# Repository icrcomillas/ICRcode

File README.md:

#  ICRcode
Entorno de desarrollo del ICAI Club de Robótica

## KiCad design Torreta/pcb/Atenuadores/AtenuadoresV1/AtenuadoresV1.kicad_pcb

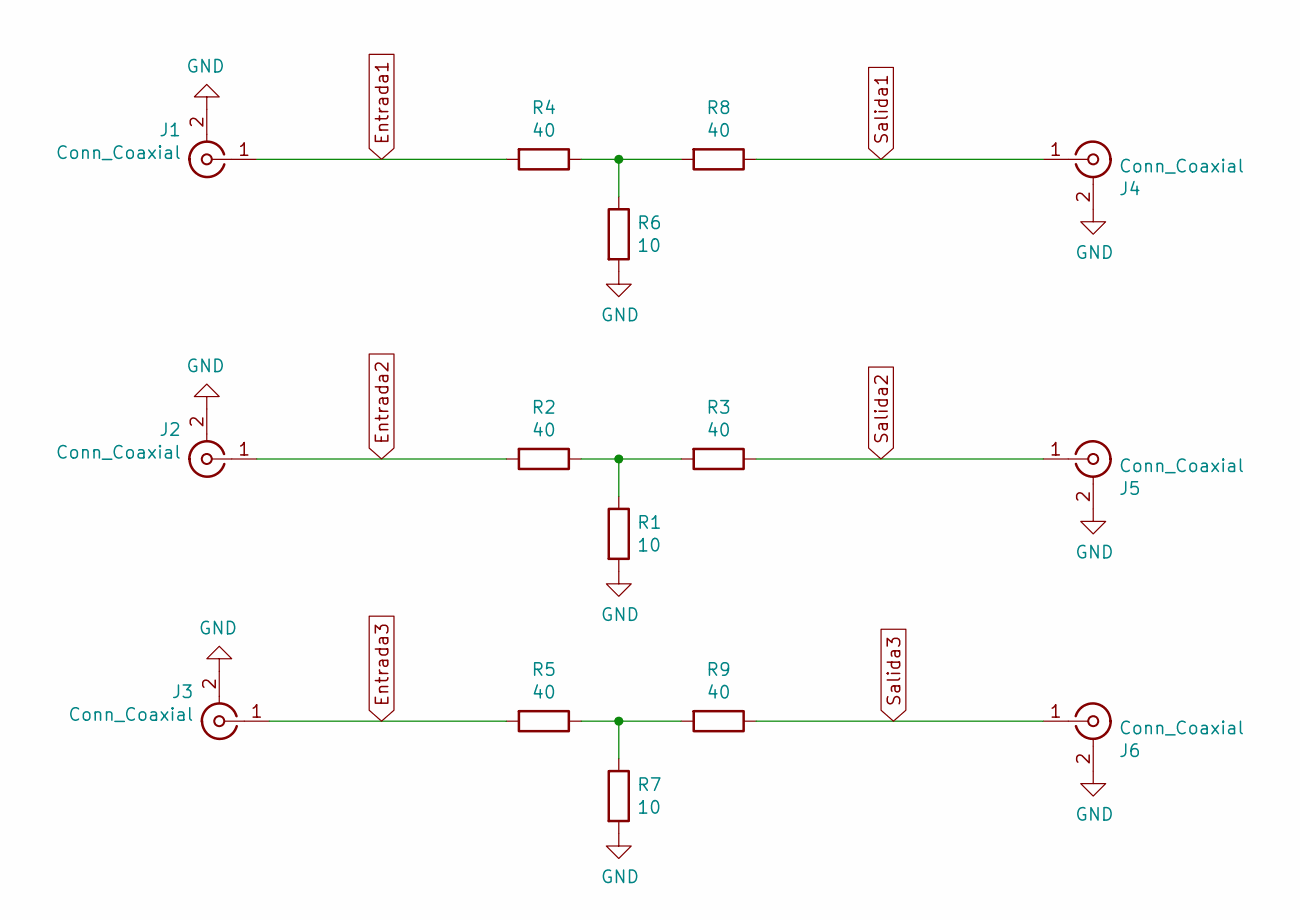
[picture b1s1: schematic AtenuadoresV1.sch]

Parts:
J1, J2, J3, J4, J5, J6: Conn_Coaxial; SMA_Amphenol_132289_EdgeMount
R1, R6, R7: 10; R_Axial_DIN0309_L9.0mm_D3.2mm_P12.70mm_Horizontal
R2, R3, R4, R5, R8, R9: 40; R_Axial_DIN0309_L9.0mm_D3.2mm_P12.70mm_Horizontal

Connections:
Entrada1: J1.1 (In), R4.2
Entrada2: J2.1 (In), R2.2
Entrada3: J3.1 (In), R5.2
GND: J1.2 (Ext), J2.2 (Ext), J3.2 (Ext), J4.2 (Ext), J5.2 (Ext), J6.2 (Ext), R1.2, R6.2, R7.2
unnamed: R1.1, R2.1, R3.2
unnamed: R4.1, R6.1, R8.2
unnamed: R5.1, R7.1, R9.2
Salida1: J4.1 (In), R8.1
Salida2: J5.1 (In), R3.1
Salida3: J6.1 (In), R9.1

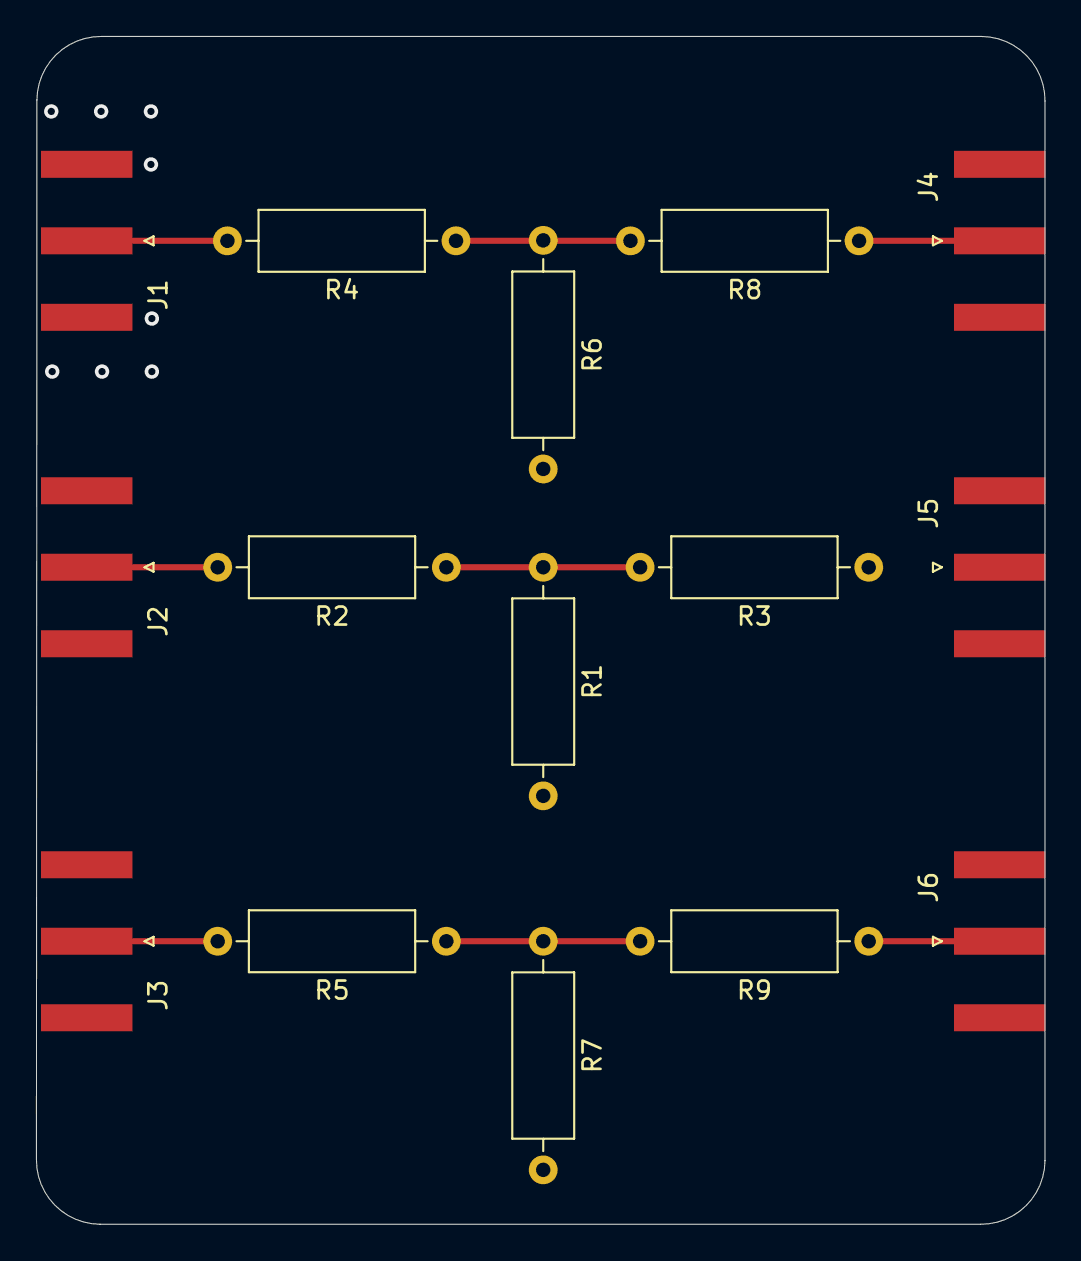
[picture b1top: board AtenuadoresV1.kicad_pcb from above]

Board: 4 copper layers, 56.0 x 66.0 mm, 15 parts (0 on the bottom side), 10 nets.

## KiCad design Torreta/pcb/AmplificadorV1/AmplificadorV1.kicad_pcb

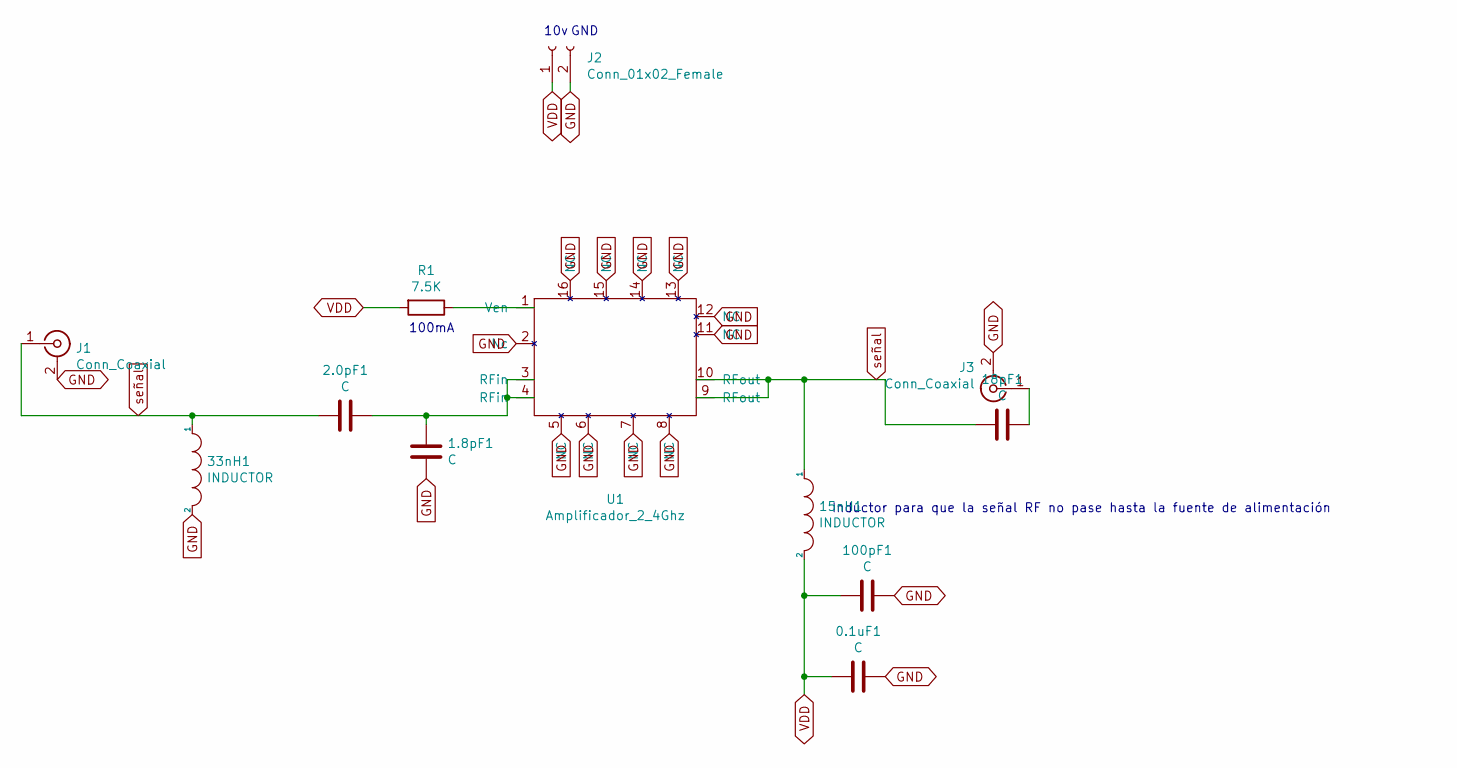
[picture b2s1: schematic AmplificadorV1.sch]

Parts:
0.1uF1: C; C_0402_1005Metric
1.8pF1: C; C_0603_1608Metric
2.0pF1, 100pF1: C; C_0805_2012Metric
15nH1, 33nH1: INDUCTOR; L_0402_1005Metric
18pF1: C; C_1206_3216Metric
J1, J3: Conn_Coaxial; SMA_Samtec_SMA-J-P-X-ST-EM1_EdgeMount
J2: Conn_01x02_Female; TerminalBlock_bornier-2_P5.08mm
R1: 7.5K; R_0603_1608Metric
U1: Amplificador_2_4Ghz; QFN-16-1EP_3x3mm_P0.5mm_EP1.75x1.75mm

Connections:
GND: 0.1uF1.1, 1.8pF1.2, 33nH1.2, 100pF1.1, J1.2 (Ext), J2.2, J3.2 (Ext)
unnamed: 1.8pF1.1, 2.0pF1.1, U1.3 (RFin), U1.4 (RFin)
unnamed: 18pF1.1, J3.1 (In)
unnamed: R1.1, U1.1 (Ven)
VDD: 0.1uF1.2, 15nH1.2, 100pF1.2, J2.1, R1.2
señal: 2.0pF1.2, 15nH1.1, 18pF1.2, 33nH1.1, J1.1 (In), U1.9 (RFout), U1.10 (RFout)

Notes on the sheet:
10v
GND
Inductor para que la señal RF no pase hasta la fuente de alimentación
100mA

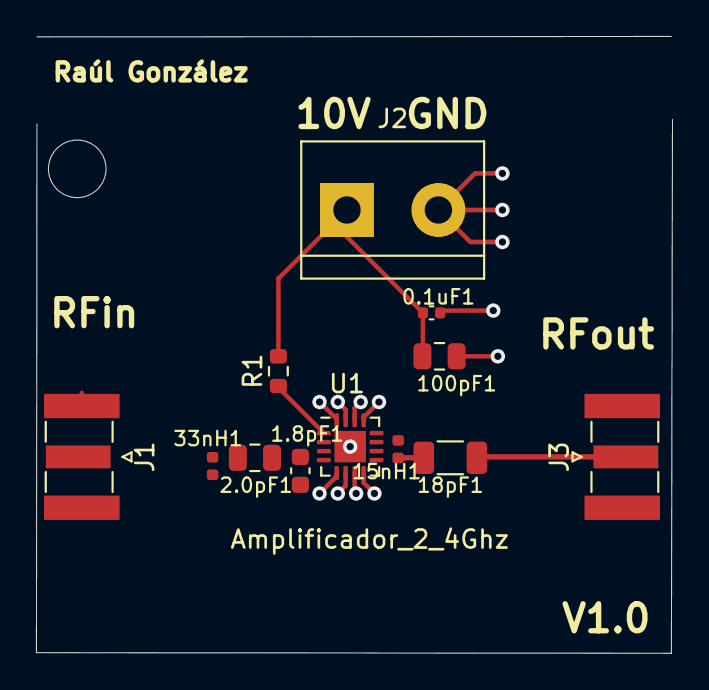
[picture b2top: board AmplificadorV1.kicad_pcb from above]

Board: 4 copper layers, 35.3 x 34.3 mm, 13 parts (0 on the bottom side), 6 nets.

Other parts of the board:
 : MountingHole_3.2mm_M3

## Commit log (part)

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2019-01-30 Update prueba
2019-01-30 Prueba permisos
2019-01-30 prueba Miguel
2019-02-03 Comprobar permisos de edición
2019-02-03 Create Prueba2
2019-02-03 ejhgjh
2019-02-03 solucionado
2019-02-07 Creado para desarrollar las bibliotecas necesarias para ejecutar codigos de Raspbian-Python en un entorno externo al la Raspberry.
2019-02-07 Explican como hacer paquetes en python
2019-02-08 Cambia la forma de desarrllar el proyecto.
    No necesitamos crear nuestra propia biblioteca RPi.GPIO.
2019-02-08 Creación de las plantillas de Python
2019-03-30 Actualizada la estructura del gitHub
2019-03-30 Probando estructura
2019-04-14 subo lo que he hecho
2019-04-16 nuevas mejoras
2019-04-17 prueba borrado archivos
2019-04-17 pequeñas mejoras en la funcion mover_servo
2019-04-24 funcion kinetc_2d
2019-05-19 nueva organizacion de codigo
2019-05-19 pruebas de driver
2019-05-19 pruebas con puerto i2c
2019-05-21 configuracion puerto i2c
2019-06-19 little tunning
2019-06-19 finalizacion de mover_servo
2019-07-02 pruebas mover_servo
2019-07-02 modificacion de la funcion calcular_pulso
2019-07-02 cambio a modo prueba
2019-07-02 calibracion angulos
2019-07-03 conexion acelerometro
2019-07-03 adaptación funcion acelerometro
2019-07-03 correcion errores
2019-07-03 pruebas
2019-07-04 calibracion acelerometro
2019-07-11 estructura del codigo del velocista definida
2019-07-15 cambios generales en la estructura de codigo
2019-07-16 Comuicacion exterior
    Se ha añadido una primera version de los driver encargados de la entrada y salida GPIO de la raspbery
2019-07-23 mejoras generales
2019-07-31 correccion de errores en las variables
2019-07-31 cambio de direcciones
2019-07-31 correccion de errores
2019-07-31 identacion corregida
2019-07-31 errores varios
2019-08-14 pruebas de direcciones
2019-08-14 errores
2019-09-01 codigo pruebas
    es el codigo del velocista con dos IR y no el array de sensores. Esta el archivo test, que funciona y es solo un archivo, y luego estan el resto que va por paquetes y hay que mejorar
2019-09-04 solución errores sintaxis
2019-09-06 reestructuración
2019-09-06 modelos 3d
2019-09-08 creacion de carpetas
2019-09-08 nuevo fichero documentacion
2019-09-12 Corregidos errores de sintaxis
2019-09-12 Volcado el contenido del drive
    *Normativa
    *Imagen_y_Diseño
    *Documentación generl
2019-09-14 implementacion sockets
2019-09-14 correccion errores sockets
2019-09-24 actualizacion de la documentacion
2019-09-25 fichero BOM
2019-09-27 direcciones driver y giro
2019-09-27 correcion bugs
2019-09-27 correccion bugs
2019-09-27 revision funcion giro
2019-09-27 declaracion variables globales [giro]
2019-09-27 identacion correcta
2019-09-29 libreria mpu6050
2019-09-30 feria asociaciones
2019-09-30 problemas conexion servos
2019-10-01 asociaciones
2019-10-20 prueba conexiones
2019-10-20 prueba giroscopio
2019-10-22 inplementacion json
2019-10-23 reunion
2019-10-23 actualizado reunion
2019-10-26 Código de prueba para la revisión del sensor IR.
2019-10-26 Prueba de descarga de condensador con resultado. Error. Conclusiones.
2019-10-29 componentes
2019-10-29 componentes y bugs
2019-10-29 fichero json
2019-10-29 json con comas
2019-10-29 Actualizada libreria del QTR
2019-10-31 Tiempo de lectura muy mejorado. Hasta 0.75ms.
2019-10-31 Ensayo final del sensor IR con medidas. ¡Éxito!
2019-11-03 Tiempos finales de lectura.
2019-11-04 Actualizada la documentación de gestión
2019-11-07 Actualizada estructura de gestión de componentes
2019-11-07 Actualizado links con información de otros equipos
2019-11-09 Pruebas con clase Sensor.
2019-11-09 prueba sincronizacion github en la raspberry
2019-11-09 prueba github
2019-11-10 Version final (con suerte) de la clase sensor
2019-11-14 cambios documentación
2019-11-23 cambios menores
2019-11-26 Actualizada documentación sobre la competición ASTI ROBOTICS
2019-12-21 ficheros de simulacion
2020-01-03 inteligencia artificial
2020-01-03 arreglos ai
2020-01-04 introduccion nuevo entorno
2020-01-09 mejoras ai
2020-01-17 mejoras en el score
2020-01-19 cambios en el grabado de archivos
2020-01-20 guardado de modelos
2020-02-14 Nueva version con dimension de entrada reducida
2020-02-14 Logo 4 en pequeño para el readme
2020-02-14 logo rescalado para readme
2020-02-15 implementacion sockets con paradigma POO
2020-02-18 nueva version diseño
2020-02-26 nueva organizacion
    Nueva organización de ficheros 3d.
    Clases adaptadas a paradigma POO
    Actualización documentación
2020-03-09 Cambios menores de estilo, y reorganizacion de ficheros
2020-03-09 retoque ai
2020-03-11 Mi querida aportacion
    pull request
2020-03-12 diseños 3d
2020-03-12 correcion parametros
2020-03-12 actualizacion documentacion
2020-03-15 nueva clase servo
2020-03-16 correcion errores sintaxis
2020-03-22 Marcado de piezas impresas
2020-03-22 Cambio para que aparezca readme
2020-03-23 Actualizadas piezas impresas
2020-03-23 reduccion red neuronal, y mayor reduccion de epsilon
2020-03-23 cambio reward
2020-03-23 simulacion 23/3/20
2020-03-25 mejoras
2020-03-27 implementación fuerzas externas
2020-03-27 licencia
2020-04-15 video y gif
2020-06-05 preparacion ros
2020-06-05 prueba comunicacion
2020-06-05 prueba socket
2020-06-05 error import
2020-06-05 cambio direcciones
2020-06-05 prueba enviar mensaje a varios usuarios
2020-06-05 cambios
2020-06-05 fail conection check
2020-06-05 add cerrrar conexion
2020-06-05 close routine
2020-06-06 giro check
2020-06-06 correcion sintaxis
2020-06-07 Ficheros urdf nuevos
2020-06-07 meshes for urdf
2020-06-07 cabeza
2020-06-07 arreglo piezas
2020-06-11 preparacionRos
2020-06-11 Preparacion para ros
2020-06-11 preparacion de comunicacion para ros
2020-06-11 toques finales para comunicacion con ros
2020-06-11 actualizacion disenos 3d
2020-06-11 finalizacion comunicacion con ros
2020-06-11 correcion error
2020-06-11 actualizacion
2020-06-11 Casi preparado para ros
2020-06-15 cambio documentacion
2020-06-21 adaptacion de giroscopio a ros
2020-06-23 fichero prueba drivers
2020-06-23 incompatibilidad python3
2020-06-23 incompatibilidades de python2 y python 3
2020-06-23 eliminacion caracteres no ascii
2020-06-24 Nueva estructura de paquetes para Ros
2021-03-15 Nuevo proyecto Torreta antidrones
2021-03-15 Prueba de nuevo branch
2021-03-15 hola
2021-03-16 Fichero para realizar toda la configuracion de forma automatica
2021-03-16 reorganizacion
2021-03-16 Cambios fichero
2021-03-16 Limpieza codigo
2021-03-16 Arreglo problemas version pip
2021-03-16 add autoremove
2021-03-19 instalacion pyadi-iio
2021-03-19 inicio codigo placa
2021-03-19 fichero prueba
2021-03-19 claridad codigo
2021-03-21 Setter ganancia
2021-03-21 funcionalidad añadida
2021-03-21 correccion errores
2021-03-21 Correcion ganancia recepcion
2021-03-21 Más métodos
2021-03-21 metodos staticos
2021-03-21 correccion sintaxis
2021-03-21 implementacion logica datos
2021-03-23 logica hilos implementada
2021-03-23 preparacion mostrar Grafica
2021-03-23 correccion error
2021-03-24 Hilo Graficas
2021-03-27 funcionamiento grafica dinamica
2021-03-31 representacion espectro tiempo real
2021-03-31 optimizacion
2021-03-31 simplificacion
2021-04-01 Función análisis Espectro
2021-04-01 Adaptacion python3.7
2021-04-01 final
2021-04-03 Errores ejecucion corregidos
2021-04-03 guardado valores implementado
2021-04-03 Preparacion funcionalidad placa
2021-04-03 Del hilo control
2021-04-03 Parametros prueba
2021-04-03 Calculo db
2021-04-03 errores minimos
2021-04-04 Cambio frecuencia
2021-04-04 Salvado de datos
2021-04-05 Prueba rendimiento
2021-04-05 limpieza
2021-04-05 cambios frecuencias
2021-04-05 error samplerate
2021-04-05 Mejora rendimiento
2021-04-05 cambios parametros
2021-04-05 error
2021-04-05 generacion ruido y analisis espectral
2021-04-05 procesado señal
2021-04-07 creación pcb
2021-04-09 Mediciones antena
2021-05-23 diseño pcb y reestructuración código
2021-05-28 Reoorganización codigo
2021-05-29 cambios software control
2021-05-29 incorporacion estados
2021-05-29 eliminar operaciones.py
2021-05-30 Maquina de estados v0.1
2021-05-30 Actualización maquina de estados v0.2
2021-05-30 Actualización de la maquina de estados v0.3
2021-05-30 Actualizacion de la maquina de estados v0.4
2021-05-30 Actualización maquina de estados v0.5
2021-05-30 Actualizacion Domingo 30M
2021-06-07 Generacion de ruido en el main v1
2021-06-07 nueva placa
2021-06-07 fichero test
2021-06-08 Arreglos para que funcione
2021-06-09 cambio en el main (sistema como var global)
2021-06-13 Detección drones en streaming
    De momento usa la webcam del ordenador para detectar en streaming.
    Falta entrenar la red para detectar drones
2021-06-28 Cambios varios
2021-07-27 Imagenes procesadas
2021-10-30 Revisión placa y atenuadores
2021-11-03 diseño torreta
2021-11-06 Cambio estado transmisión y prueba concepto
2021-11-09 preparación para optimización codigo
2021-11-15 datasets added
2021-11-15 new dataset
2021-11-18 reorganization
2021-11-19 data added
2021-11-28 Cambios para adaptar a jetson nano
2021-12-01 stl incluidos
2021-12-06 nueva simulacion
2021-12-12 adaptación transistor
2021-12-13 sync
2021-12-13 Nuevas versiones
2021-12-13 New Version
2021-12-13 Lineas
2021-12-20 driver preliminar
2021-12-26 Driver motores terminado
2021-12-26 add Rodamiento Base
2021-12-26 correas added
2021-12-26 arreglo driver
2021-12-26 comunicacion serial implementada
2021-12-26 move
2021-12-26 nuevos stl
